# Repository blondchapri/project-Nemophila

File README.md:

# project-Nemophila
HID system used for displaying ,acquisition and processing of vehicle data  designed for  a E-BAJA atv in accordance with SAE India rulebook 2027 
# Overview
This is a 2 board design; I have split the boards to save space and cost.\
### Board 1 utilizes: 
+ an Arduino Uno Q for all the acquisition and processing of vehicle data 
+ a MP2338GTL-Z SMPS used to power the whole system, it takes in a 12V battery and steps it down to 5v 
+ a TJA1042T_3_CM_118 CAN transceiver to collect data from all the other systems from the buggy 
+  Arduino Mega 3.2’’ TFT hat/ shield used to display relevant and specialized data and fault messages using AI models running on the Uno-Q
### Board 2 utilizes:
+ 2x HT16K33 used to drive the segment displays; it receives its 12c signal from Board 1 
+ 9x .8 inch 16 segments, one for battery SOC, one for voltage, one for battery temperature 
+ Board 2 gets its power from Board 1 

# Board 1

This is the main board of this system where all the control and computation is done\
It’s a 4 layer board, with the 2 outer layers being primarily for signals with a ground pour, layer 2 for ground, and layer 3 for +5V

## Uno-Q

I won't go into detail about it, but to know more about this banger of a single-board computer, you should [read its documentation](https://docs.arduino.cc/hardware/uno-q/#features)\
Basically, it has 2 processors, Qualcomm Dragonwing QRB2210 based on  Arm Cortex-A53 of which it has 4 cores. This runs our AI model [it can also ''play'' games](https://youtu.be/YrrqF2y-dlM?si=kdVxpX9fKiZ1ygUE) 
and the second chip is the STM32U585 microcontroller based on Arm Cortex-M33, which is used for all our embedded shenanigans

The Uno Q has the 120 highspeed pins on the underside 60 per processor and the rest in the standard Uno config on top, which are primarily STM32U585 GPIO. We used pin headers for the underside connectors and headers with jumper wires for the top GPIO pins. Most of our needs are met by the STM32 used to drive the 3.2 inch TFT and the 9 segment displays stm32 is also used for the CAN bus communication 

Highlighted parts are part of the UNO-Q subsystem.

## MP2338GTL-Z 
I mean it’s a power supply\
Why I chose it : [[insert AI’s answer]](https://github.com/blondchapri/project-Nemophila/blob/main/ai)\
it takes the 12v battery input from the xt60 and steps it down to +5V

)

## TJA1042T_3_CM_118
CAN transceiver works with both 3V3 and 5v logic, cheap and easy to find online and in offline shops!!!!! Yes please

## Arduino Mega 3.2’’ TFT hat
why specifically this one?\
Well, we needed a display I had this lying around for an unrelated personal project, and my stingy team said GIVE IT HERE. And that is why this one.\
You can learn about this display by reading the uploaded PDFs or [the LCDWIKI article](https://www.lcdwiki.com/3.2inch_Arduino_Display-Mega2560)

# Board 2

This is a 2 layer board only used for the segment display, which is why I thought not to waste money by using a 4 layer board  
It gets its power and I2C signal from board 1
HT16K33 works on 5V logic, so it needs a logic level shifter to work with UNO-Q which is present on Board 1

## why the name
I recently got into illustrated flower artworks and decided that all my projects and work will be named after cool flowers.

Why Nemophila? I absolutely adore this flower and its blue hue. I had the honour of witnessing its beauty in real life last year (2025) at Anime India Mumbai, where a Frieren cosplayer had made a tiara of them. Ever since then, their etherealness is stuck in my head. Also Rei Ayanami's hair colour is similar and gives the same feeling, and I am a big time EVA fan 

### <a href="https://github.com/blondchapri/project-Gulmohar">Project Gulmohar</a> © 2026 by <a href="https://github.com/blondchapri">shlok shukla</a> is licensed under <a href="https://creativecommons.org/licenses/by-nc-sa/4.0/">Creative Commons Attribution-NonCommercial-ShareAlike 4.0 International</a>
#

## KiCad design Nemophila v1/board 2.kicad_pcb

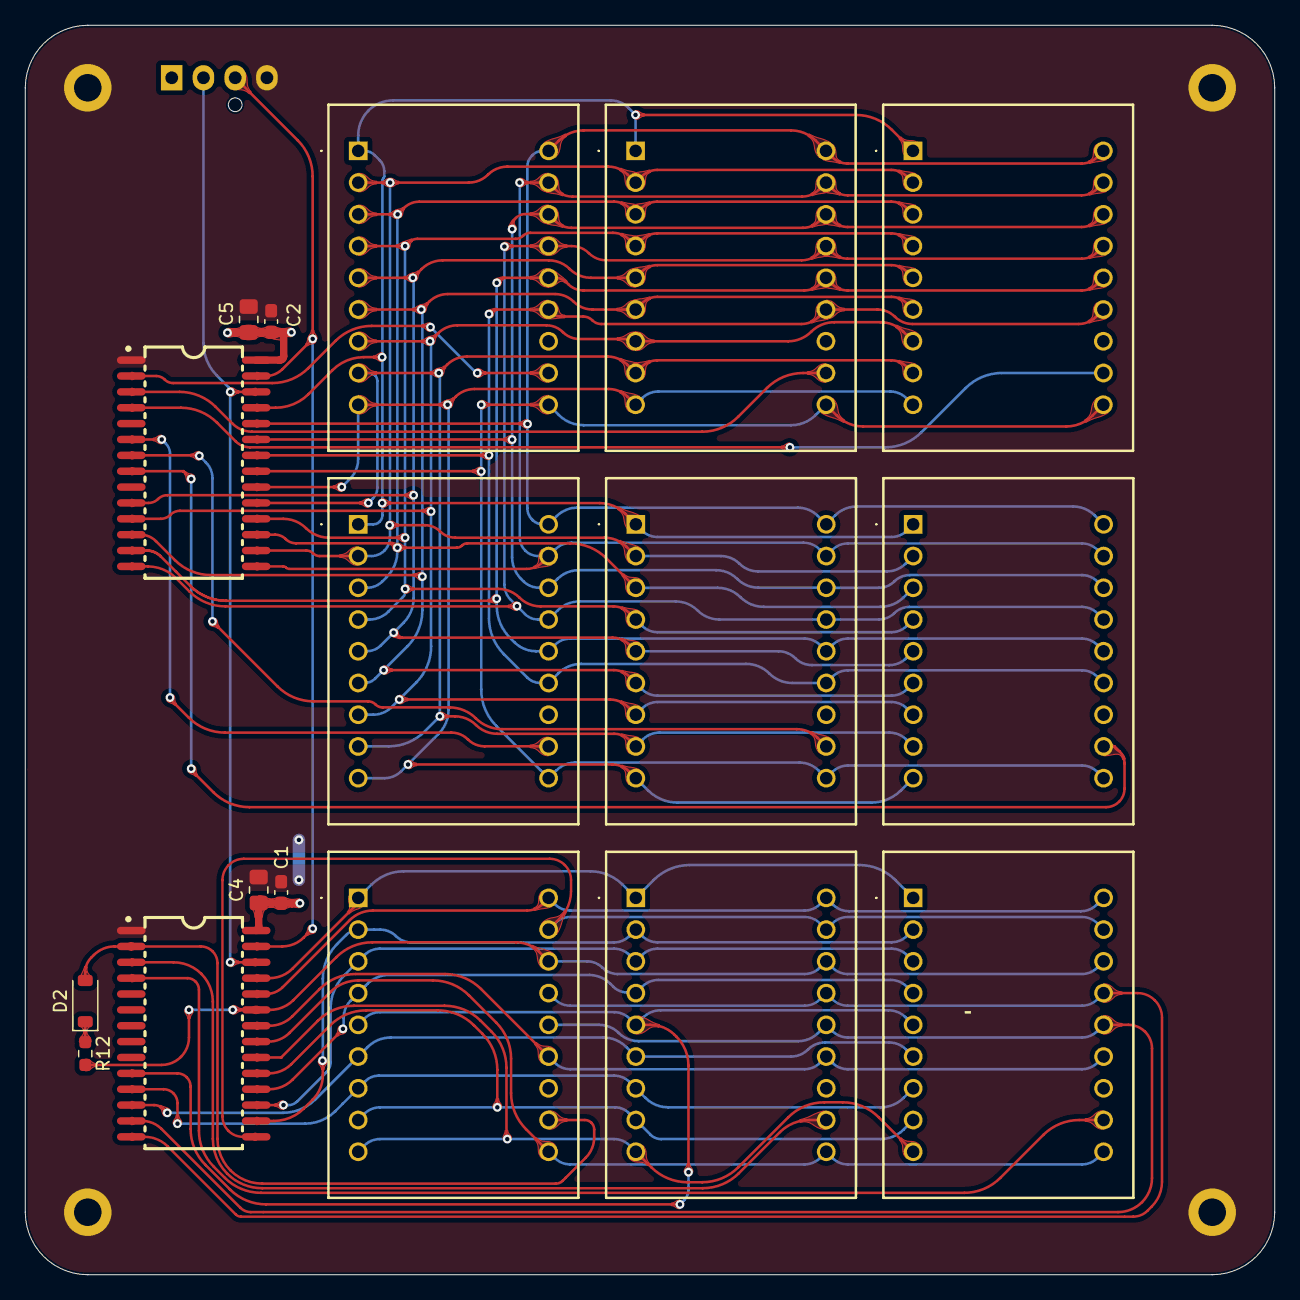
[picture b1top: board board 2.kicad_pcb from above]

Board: 2 copper layers, 100.0 x 100.0 mm, 22 parts (1 on the bottom side), 46 nets.

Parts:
C1, C2: .1 uf; C_0603_1608Metric_Pad1.08x0.95mm_HandSolder
C4, C5: 10 uf; C_0805_2012Metric_Pad1.18x1.45mm_HandSolder
D2: 1N4148W; D_SOD-123
DS1, DS2, DS3, DS5, DS6, DS7, DS9, DS10, DS11: PSC08-11YWA; PSC0811YWA
H1, H2, H3, H4: MountingHole_Pad; MountingHole_2.2mm_M2_DIN965_Pad
J8: Conn_01x04_Socket; FanPinHeader_1x04_P2.54mm_Vertical
R12: 39k; R_0603_1608Metric_Pad0.98x0.95mm_HandSolder
U2, U3: SOP-28_L18.5-W7.8-P1.27-LS10.6-BL

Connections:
+5V: C1.1, C2.1, C4.1, C5.1, J8.1, U2.28 (VDD), U3.28 (VDD)
A: DS1.1 (A_A), DS2.1 (A_A), DS5.1 (A_A), DS6.1 (A_A), DS9.1 (A_A), DS10.1 (A_A), U2.25 (ROW0/A2)
A2: DS3.1 (A_A), DS7.1 (A_A), DS11.1 (A_A), U3.25 (ROW0/A2)
B: DS1.18 (A_B), DS2.18 (A_B), DS5.18 (A_B), DS6.18 (A_B), DS9.18 (A_B), DS10.18 (A_B), U2.24 (ROW1/A1)
B2: DS3.18 (A_B), DS7.18 (A_B), DS11.18 (A_B), U3.24 (ROW1/A1)
C: DS1.16 (A_C), DS2.16 (A_C), DS5.16 (A_C), DS6.16 (A_C), DS9.16 (A_C), DS10.16 (A_C), U2.23 (ROW2/A0)
C2: DS3.16 (A_C), DS7.16 (A_C), DS11.16 (A_C), R12.2, U3.23 (ROW2/A0)
D: DS1.13 (A_D), DS2.13 (A_D), DS5.13 (A_D), DS6.13 (A_D), DS9.13 (A_D), DS10.13 (A_D), U2.22 (ROW3/K1)
D2: DS3.13 (A_D), DS7.13 (A_D), DS11.13 (A_D), U3.22 (ROW3/K1)
E: DS1.10 (A_E), DS2.10 (A_E), DS5.10 (A_E), DS6.10 (A_E), DS9.10 (A_E), DS10.10 (A_E), U2.21 (ROW4/K2)
E2: DS3.10 (A_E), DS7.10 (A_E), DS11.10 (A_E), U3.21 (ROW4/K2)
F: DS1.9 (A_F), DS2.9 (A_F), DS5.9 (A_F), DS6.9 (A_F), DS9.9 (A_F), DS10.9 (A_F), U2.20 (ROW5/K3)
F2: DS3.9 (A_F), DS7.9 (A_F), DS11.9 (A_F), U3.20 (ROW5/K3)
G: DS1.8 (A_G), DS2.8 (A_G), DS5.8 (A_G), DS6.8 (A_G), DS9.8 (A_G), DS10.8 (A_G), U2.19 (ROW6/K4)
G2: DS3.8 (A_G), DS7.8 (A_G), DS11.8 (A_G), U3.19 (ROW6/K4)
GND: C1.2, C2.2, C4.2, C5.2, H1.1 (1_1), H2.1 (1_1), H3.1 (1_1), H4.1 (1_1), J8.4, U2.1 (VSS), U3.1 (VSS)
H: DS1.4 (A_H), DS2.4 (A_H), DS5.4 (A_H), DS6.4 (A_H), DS9.4 (A_H), DS10.4 (A_H), U2.18 (ROW7/K5)
H2: DS3.4 (A_H), DS7.4 (A_H), DS11.4 (A_H), U3.18 (ROW7/K5)
K: DS1.3 (A_K), DS2.3 (A_K), DS5.3 (A_K), DS6.3 (A_K), DS9.3 (A_K), DS10.3 (A_K), U2.17 (ROW8/K6)
K2: DS3.3 (A_K), DS7.3 (A_K), DS11.3 (A_K), U3.17 (ROW8/K6)
M: DS1.2 (A_M), DS2.2 (A_M), DS5.2 (A_M), DS6.2 (A_M), DS9.2 (A_M), DS10.2 (A_M), U2.16 (ROW9/K7)
M2: DS3.2 (A_M), DS7.2 (A_M), DS11.2 (A_M), U3.16 (ROW9/K7)
N: DS1.17 (A_N), DS2.17 (A_N), DS5.17 (A_N), DS6.17 (A_N), DS9.17 (A_N), DS10.17 (A_N), U2.15 (ROW10/K8)
N2: DS3.17 (A_N), DS7.17 (A_N), DS11.17 (A_N), U3.15 (ROW10/K8)
unnamed: D2.1 (K), R12.1
P: DS1.15 (A_P), DS2.15 (A_P), DS5.15 (A_P), DS6.15 (A_P), DS9.15 (A_P), DS10.15 (A_P), U2.14 (ROW11/K9)
P2: DS3.15 (A_P), DS7.15 (A_P), DS11.15 (A_P), U3.14 (ROW11/K9)
R: DS1.14 (A_R), DS2.14 (A_R), DS5.14 (A_R), DS6.14 (A_R), DS9.14 (A_R), DS10.14 (A_R), U2.13 (ROW12/K10)
R2: DS3.14 (A_R), DS7.14 (A_R), DS11.14 (A_R), U3.13 (ROW12/K10)
S: DS1.6 (A_S), DS2.6 (A_S), DS5.6 (A_S), DS6.6 (A_S), DS9.6 (A_S), DS10.6 (A_S), U2.12 (ROW13/K11)
S2: DS3.6 (A_S), DS7.6 (A_S), DS11.6 (A_S), U3.12 (ROW13/K11)
SCL: J8.2, U2.26 (SCL), U3.26 (SCL)
SDA: J8.3, U2.27 (SDA), U3.27 (SDA)
SET 1 DIG 1: DS1.11 (COM_K), U2.2 (COM0/AD)
SET 1 DIG 2: DS5.11 (COM_K), U2.3 (COM1/KS0)
SET 1 DIG 3: DS9.11 (COM_K), U2.4 (COM2/KS1)
SET 2 DIG 1: DS2.11 (COM_K), U2.6 (COM4)
SET 2 DIG 2: DS6.11 (COM_K), U2.7 (COM5)
SET 2 DIG 3: DS10.11 (COM_K), U2.8 (COM6)
SET 3 DIG 1: D2.2 (A), DS3.11 (COM_K), U3.2 (COM0/AD)
SET 3 DIG 2: DS7.11 (COM_K), U3.3 (COM1/KS0)
SET 3 DIG 3: DS11.11 (COM_K), U3.4 (COM2/KS1)
T: DS1.7 (A_T), DS2.7 (A_T), DS5.7 (A_T), DS6.7 (A_T), DS9.7 (A_T), DS10.7 (A_T), U2.11 (ROW14/K12)
T2: DS3.7 (A_T), DS7.7 (A_T), DS11.7 (A_T), U3.11 (ROW14/K12)
U: DS1.5 (A_U), DS2.5 (A_U), DS5.5 (A_U), DS6.5 (A_U), DS9.5 (A_U), DS10.5 (A_U), U2.10 (ROW15/K13/INT)
U2: DS3.5 (A_U), DS7.5 (A_U), DS11.5 (A_U), U3.10 (ROW15/K13/INT)

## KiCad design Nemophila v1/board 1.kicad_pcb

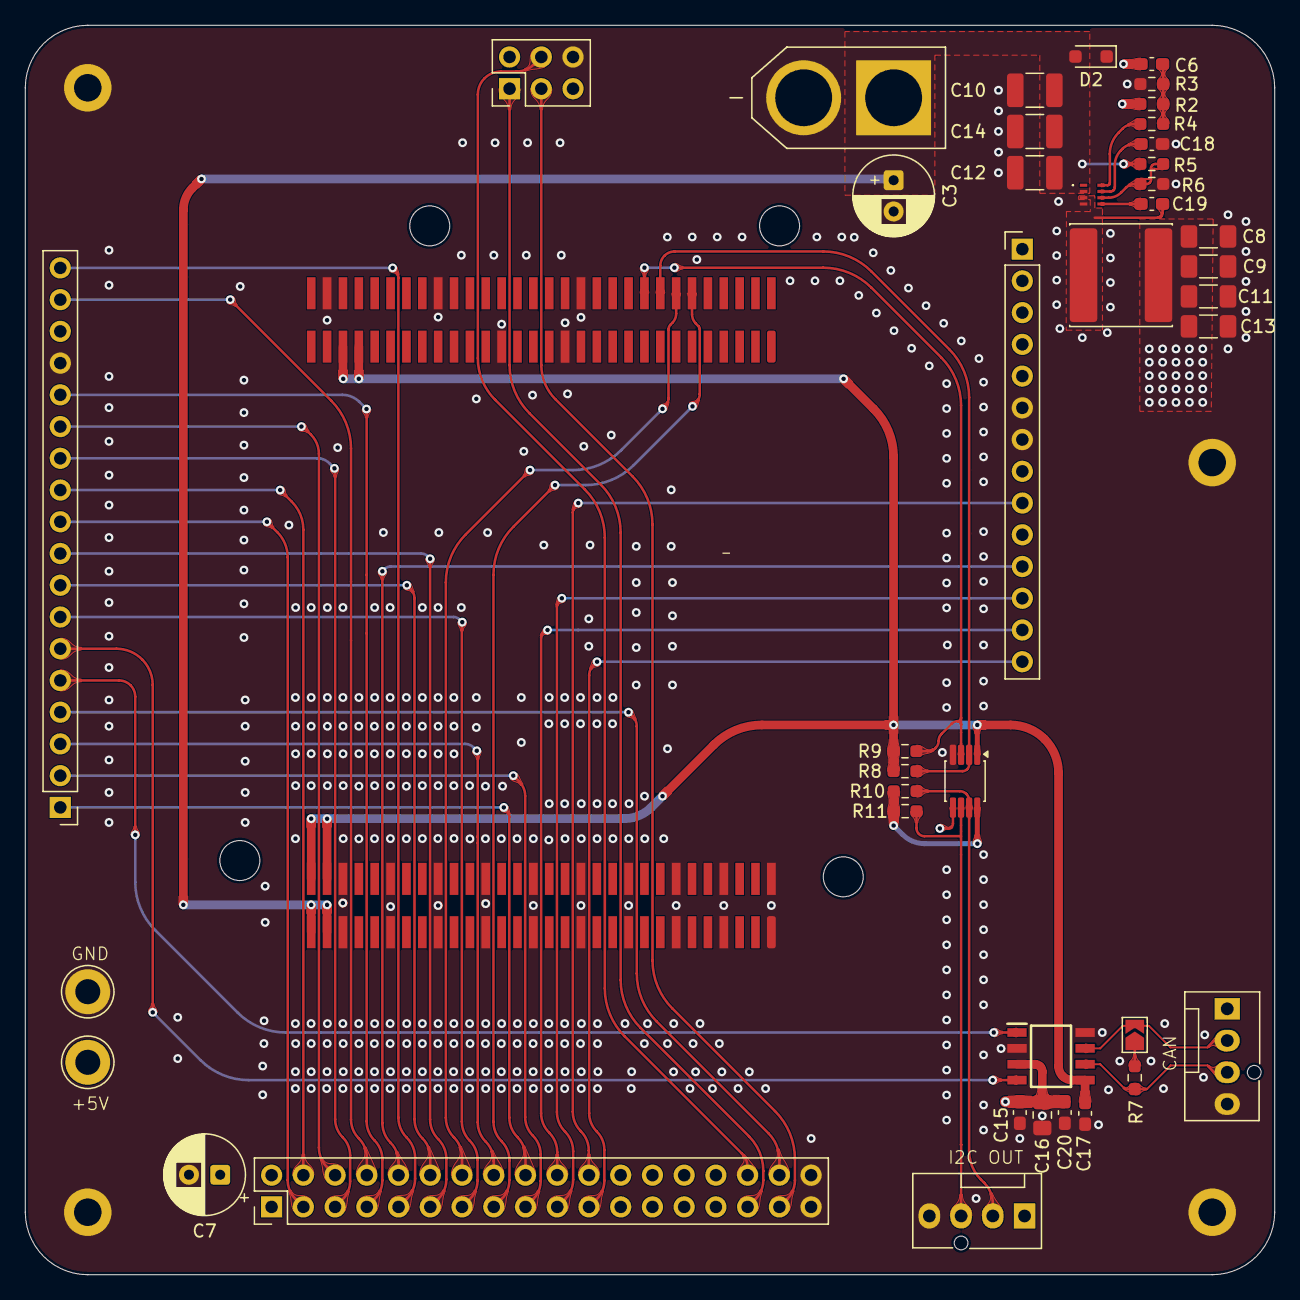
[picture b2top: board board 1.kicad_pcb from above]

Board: 4 copper layers, 100.0 x 100.0 mm, 46 parts (0 on the bottom side), 43 nets.

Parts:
C3, C7: 100 uf; CP_Radial_D6.3mm_P2.50mm
C6: 300pf; C_0603_1608Metric_Pad1.08x0.95mm_HandSolder
C8, C9, C11, C13: 22uf; C_1206_3216Metric_Pad1.33x1.80mm_HandSolder
C10: 10 uf; C_1210_3225Metric_Pad1.33x2.70mm_HandSolder
C12: .1 uf; C_1210_3225Metric_Pad1.33x2.70mm_HandSolder
C14: 22uf; C_1210_3225Metric_Pad1.33x2.70mm_HandSolder
C15: 1uf; C_0603_1608Metric_Pad1.08x0.95mm_HandSolder
C16: 10uf; C_0805_2012Metric_Pad1.18x1.45mm_HandSolder
C17, C20: .1uf; C_0603_1608Metric_Pad1.08x0.95mm_HandSolder
C18: 100nf; C_0603_1608Metric_Pad1.08x0.95mm_HandSolder
C19: .1 uf; C_0603_1608Metric_Pad1.08x0.95mm_HandSolder
D2: D_TVS; D_SOD-323_HandSoldering
H1, H2, H3, H4: MountingHole_Pad; MountingHole_2.2mm_M2_DIN965_Pad
IC1: MP2338GTL-Z; MP2338GTLZ
IC2: TJA1042T_3_CM,118; SOIC127P600X175-8N
J1: UNO_Q; UNO_Q_Mezzanine_JMISC+JMEDIA
J2: JDIGITAL; PinHeader_1x18_P2.54mm_Vertical
J3: JANALOG; PinHeader_1x14_P2.54mm_Vertical
J5: XT60-M; AMASS_XT60-M
J6: display 16bit output; PinHeader_2x18_P2.54mm_Vertical
J7, J8: Conn_01x04_Socket; FanPinHeader_1x04_P2.54mm_Vertical
J9: JSPI; PinHeader_2x03_P2.54mm_Vertical
JP2: Jumper_Measure_Open; SolderJumper-2_P1.3mm_Open_TrianglePad1.0x1.5mm
L1: 6.85uh; L_Sunlord_SWPA8040S
R2: 90.9kΩ; R_0603_1608Metric_Pad0.98x0.95mm_HandSolder
R3, R4: 10kΩ; R_0603_1608Metric_Pad0.98x0.95mm_HandSolder
R5: 191kΩ; R_0603_1608Metric_Pad0.98x0.95mm_HandSolder
R6: 49.9kΩ; R_0603_1608Metric_Pad0.98x0.95mm_HandSolder
R7: 120R; R_0603_1608Metric_Pad0.98x0.95mm_HandSolder
R8, R9, R10, R11: 4K7; R_0603_1608Metric_Pad0.98x0.95mm_HandSolder
TP1, TP2: TestPoint; TestPoint_Loop_D3.80mm_Drill2.0mm
U1: TCA9517ADGK; VSSOP-8_3x3mm_P0.65mm

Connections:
+3V3: C17.2, IC2.5 (VIO), J1.A53 (+3V3), J1.A55 (+3V3), J1.B58 (+3V3), J1.B60 (+3V3), R8.2, R9.2, U1.1 (VCCA)
+5V: C6.1, C7.1, C8.1, C9.1, C11.1, C13.1, C15.1, C16.1, C20.2, IC2.3 (VCC), J6.1, J6.2, J7.1, J8.1, L1.1, R2.1, R10.2, R11.2, TP1.1 (1_1), U1.5 (EN), U1.8 (VCCB)
+12V: C3.1, C10.1, C12.1, C14.1, D2.2 (A2), IC1.2 (VIN), J1.B57 (VIN), J1.B59 (VIN), J5.P (POS), R5.1
/sw: C19.2, IC1.3 (SW), L1.2
DB1: J2.2, J6.17
DB2: J2.3, J6.16
DB3: J1.A12 (MCU_PE7), J6.15
DB4: J1.A14 (MCU_PE8), J6.14
DB5: J2.7, J6.13
DB6: J2.8, J6.12
DB7: J2.9, J6.11
DB8: J2.10, J6.3
DB9: J2.11, J6.4
DB10: J2.12, J6.5
DB11: J2.13, J6.6
DB12: J2.14, J6.7
DB13: J2.17, J6.8
DB14: J2.18, J6.9
DB15: J3.11, J6.10
DBO: J2.1, J6.18
GND: C3.2, C7.2, C8.2, C9.2, C10.2, C11.2, C12.2, C13.2, C14.2, C15.2, C16.2, C17.1, C18.2, C20.1, D2.1 (A1), H1.1 (1_1), H2.1 (1_1), H3.1 (1_1), H4.1 (1_1), IC1.4 (GND), IC2.2 (GND), IC2.8 (STB), J1.A26 (GND), J1.A27 (GND), J1.A35 (GND), J1.A44 (GND), J1.A58 (GND), J1.B1 (GND), J1.B2 (GND), J1.B7 (GND), J1.B8 (GND), J1.B13 (GND), J1.B14 (GND), J1.B19 (GND), J1.B20 (GND), J1.B25 (GND), J1.B26 (GND), J1.B31 (GND), J1.B32 (GND), J1.B37 (GND), J1.B38 (GND), J1.B43 (GND), J1.B44 (GND), J1.B49 (GND), J1.B50 (GND), J1.B55 (GND), J1.B56 (GND), J2.15, J3.6, J3.7, J5.N (NEG), J6.35, J6.36, J7.4, J8.4, J9.6, R3.2, R6.2, TP2.1 (1_1), U1.4 (GND)
LCD CS: J3.14, J6.21
LCD RST: J3.9, J6.22
LCD_RS: J3.12, J6.19
LCD_WR: J3.13, J6.20
unnamed: C6.2, R2.2, R3.1, R4.1
unnamed: C19.1, IC1.5 (BST)
unnamed: IC1.6 (EN), R5.2, R6.1
unnamed: IC1.8 (FB), R4.2
unnamed: C18.1, IC1.7 (SS)
unnamed: J1.A16 (MCU_I2C4_SCL), R8.1, U1.2 (SCLA)
unnamed: J1.A18 (MCU_I2C4_SDA), R9.1, U1.3 (SDAA)
unnamed: JP2.1 (A), R7.1
SCL: J8.2, R10.1, U1.7 (SCLB)
SD CS: J2.4, J6.34
SDA: J8.3, R11.1, U1.6 (SDAB)
SPI CLK: J6.33, J9.3
SPI MISO: J6.31, J9.1
SPI_MOSI: J6.32, J9.4
can h +: IC2.7 (CANH), J7.2, JP2.2 (B)
can h -: IC2.6 (CANL), J7.3, R7.2
can rx: IC2.4 (RXD), J2.6
can tx: IC2.1 (TXD), J2.5

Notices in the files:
README.md:
https://mirrors.creativecommons.org/presskit/icons/cc.svg
https://mirrors.creativecommons.org/presskit/icons/by.svg
https://mirrors.creativecommons.org/presskit/icons/nc.svg
https://mirrors.creativecommons.org/presskit/icons/sa.svg
